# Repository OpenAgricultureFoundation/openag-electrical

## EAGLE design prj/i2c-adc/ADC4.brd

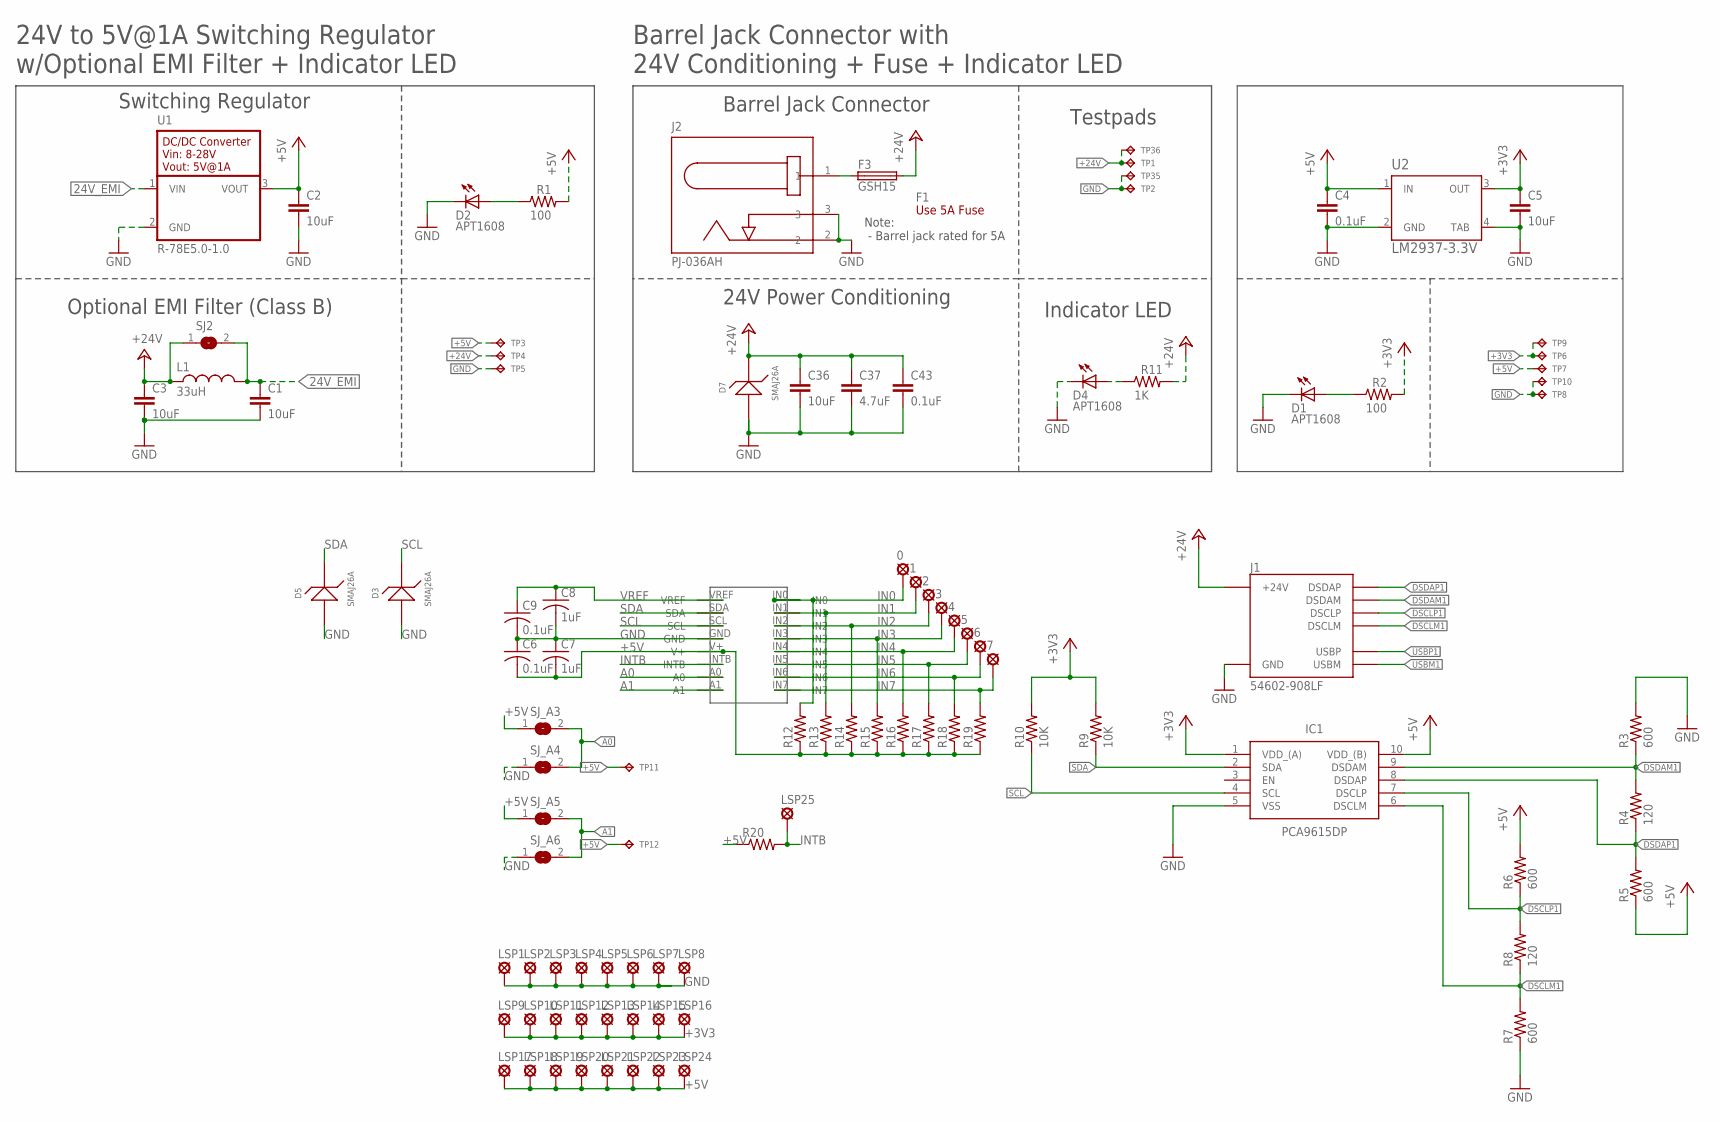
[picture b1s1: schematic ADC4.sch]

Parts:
0, 1, 2, 3, 4, 5, 6, 7: LSP13
C1, C2, C3, C5, C36: 10uF; C0805
C4, C6, C9, C43: 0.1uF; C0603
C7, C8: 1uF; C0603
C37: 4.7uF; C0805
D1, D2, D4: APT1608; CHIPLED_0603
D3, D5, D7: SMAJ26A; SMA
F1: Use 5A Fuse; FUSE-CARTRIDGE
F3: GSH15
IC1: PCA9615DP; SOP50P490X110-10N
J1: 54602-908LF; OPENAG-V1-RJ45
J2: PJ-036AH; BARREL-JACK-PJ-036AH
L1: 33uH; 29333C
LSP1, LSP2, LSP3, LSP4, LSP5, LSP6, LSP7, LSP8, LSP9, LSP10, LSP11, LSP12, LSP13, LSP14, LSP15, LSP16, LSP17, LSP18, LSP19, LSP20, LSP21, LSP22, LSP23, LSP24: LSP13
LSP25: LSP10
R1, R2: 100; RC0603N
R3, R5, R6, R7: 600; R0603
R4, R8: 120; R0603
R9, R10: 10K; R0603
R11: 1K; RC0603N
R12, R13, R14, R15, R16, R17, R18, R19, R20: R-US_R0603; R0603
SJ2: EMI-BYPASS
SJ_A3, SJ_A4, SJ_A5, SJ_A6: SOLDERJUMPERREFLOW_NOPASTE; SJ1
TP1, TP2, TP6, TP7, TP8, TP9, TP10, TP11, TP12, TP35, TP36: TPTP04R; TP04R
TP3, TP4, TP5: TPTP06R; TP06R
U1: R-78E5.0-1.0
U2: LM2937-3.3V; MP04A
U$1: ADC128D818; TSSOP16

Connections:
24V_EMI: C1.1, L1.2, SJ2.2, U1.1 (VIN)
24V_IN: F3.1, J2.1
+3V3: C5.1, IC1.1 (VDD_(A)), LSP9.MP, LSP10.MP, LSP11.MP, LSP12.MP, LSP13.MP, LSP14.MP, LSP15.MP, LSP16.MP, R2.2, R9.2, R10.2, TP6.1, TP9.1, U2.3 (OUT)
+5V: C2.1, C4.1, C6.2, C7.2, IC1.10 (VDD_(B)), LSP17.MP, LSP18.MP, LSP19.MP, LSP20.MP, LSP21.MP, LSP22.MP, LSP23.MP, LSP24.MP, R1.2, R5.1, R6.2, R12.1, R13.1, R14.1, R15.1, R16.1, R17.1, R18.1, R19.1, R20.1, SJ_A3.1, SJ_A5.1, TP3.TP, TP7.1, TP11.1, TP12.1, U1.3 (VOUT), U2.1 (IN), U$1.V+
+24V: C3.1, C36.1, C37.1, C43.1, D7.1, F3.2, J1.24V(6) (+24V), L1.1, R11.2, SJ2.1, TP1.1, TP4.TP, TP36.1
A0: SJ_A3.2, SJ_A4.2, U$1.A0
A1: SJ_A5.2, SJ_A6.2, U$1.A1
DSCLM1: IC1.6 (DSCLM), J1.DSCLM(5) (DSCLM), R7.2, R8.1
DSCLP1: IC1.7 (DSCLP), J1.DSCLP(4) (DSCLP), R6.1, R8.2
DSDAM1: IC1.9 (DSDAM), J1.DSDAM(2) (DSDAM), R3.1, R4.2
DSDAP1: IC1.8 (DSDAP), J1.DSDAP(1) (DSDAP), R4.1, R5.2
GND: C1.2, C2.2, C3.2, C4.2, C5.2, C6.1, C7.1, C8.2, C9.2, C36.2, C37.2, C43.2, D1.C, D2.C, D3.2, D4.C, D5.2, D7.2, IC1.5 (VSS), J1.GND(3) (GND), J2.2, J2.3, LSP1.MP, LSP2.MP, LSP3.MP, LSP4.MP, LSP5.MP, LSP6.MP, LSP7.MP, LSP8.MP, R3.2, R7.1, SJ_A4.1, SJ_A6.1, TP2.1, TP5.TP, TP8.1, TP10.1, TP35.1, U1.2 (GND), U2.2 (GND), U2.4 (TAB), U$1.GND
IN0: 0.MP, R12.2, U$1.IN0
IN1: 1.MP, R13.2, U$1.IN1
IN2: 2.MP, R14.2, U$1.IN2
IN3: 3.MP, R15.2, U$1.IN3
IN4: 4.MP, R16.2, U$1.IN4
IN5: 5.MP, R17.2, U$1.IN5
IN6: 6.MP, R18.2, U$1.IN6
IN7: 7.MP, R19.2, U$1.IN7
INTB: LSP25.MP, R20.2, U$1.INTB
unnamed: D1.A, R2.1
unnamed: D2.A, R1.1
unnamed: D4.A, R11.1
SCL: D3.1, IC1.4 (SCL), R10.1, U$1.SCL
SDA: D5.1, IC1.2 (SDA), R9.1, U$1.SDA
USBM1: J1.USBM(8) (USBM)
USBP1: J1.USBP(7) (USBP)
VREF: C8.1, C9.1, U$1.VREF

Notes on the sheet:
Barrel Jack Connector
Barrel Jack Connector with 24V Conditioning + Fuse + Indicator LED
24V Power Conditioning
Indicator LED
Testpads
Note: - Barrel jack rated for 5A
24V to 5V@1A Switching Regulator w/Optional EMI Filter + Indicator LED
Switching Regulator
Optional EMI Filter (Class B)

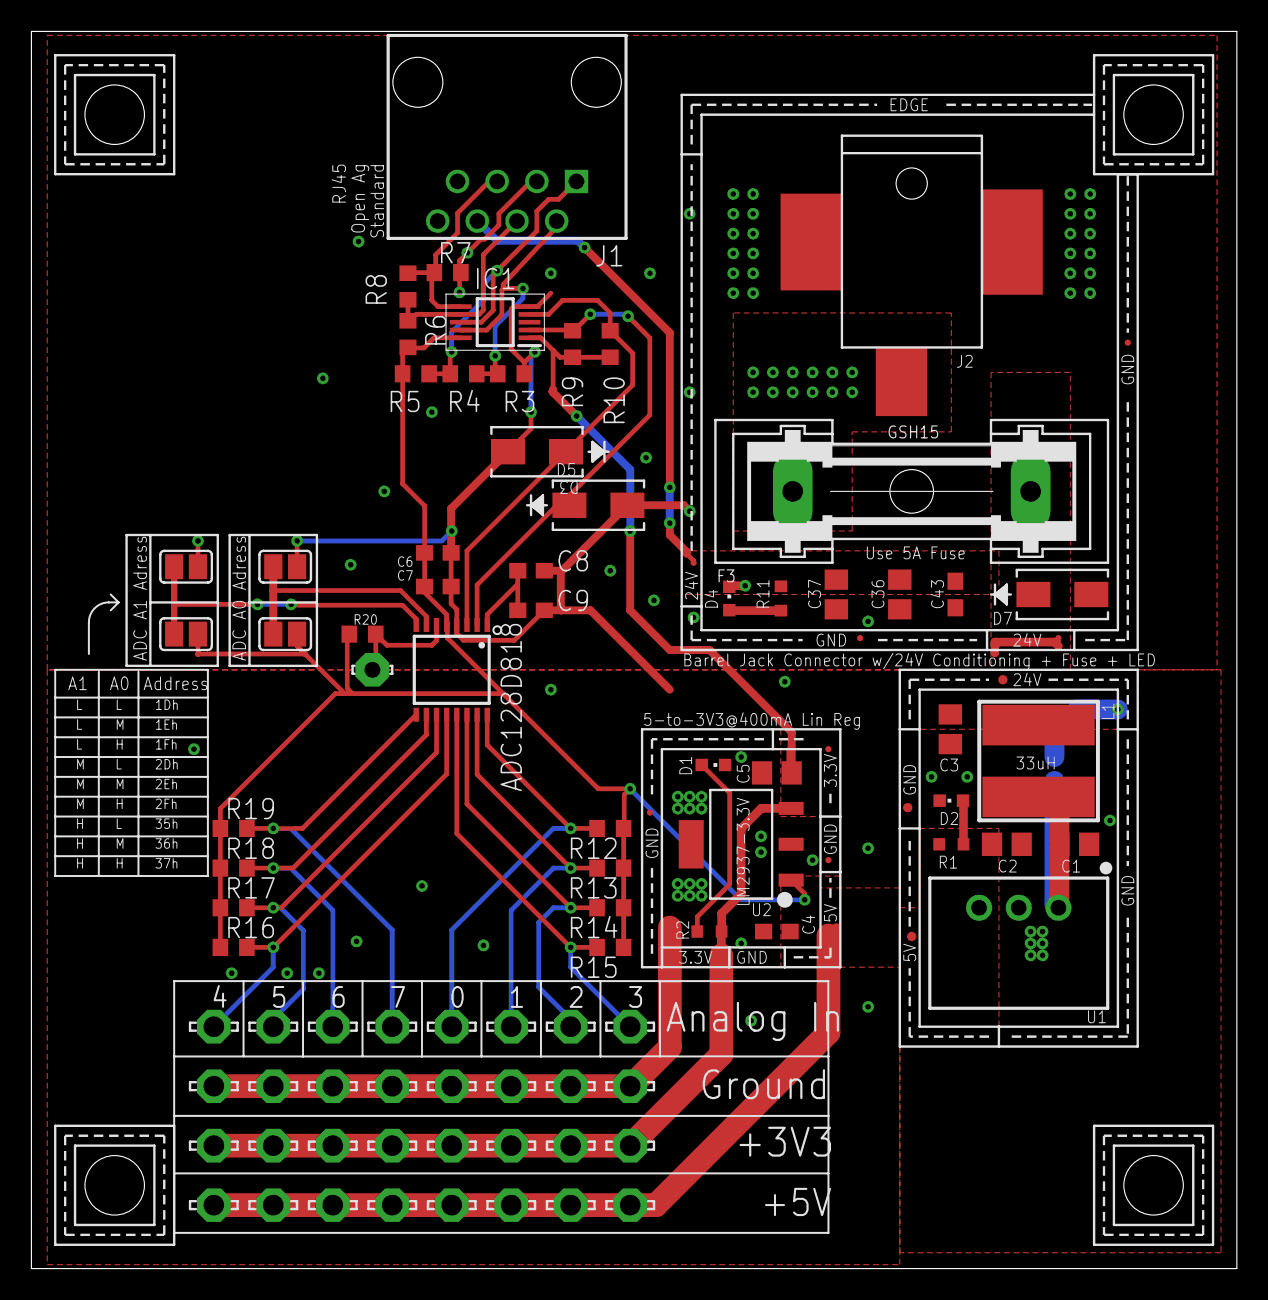
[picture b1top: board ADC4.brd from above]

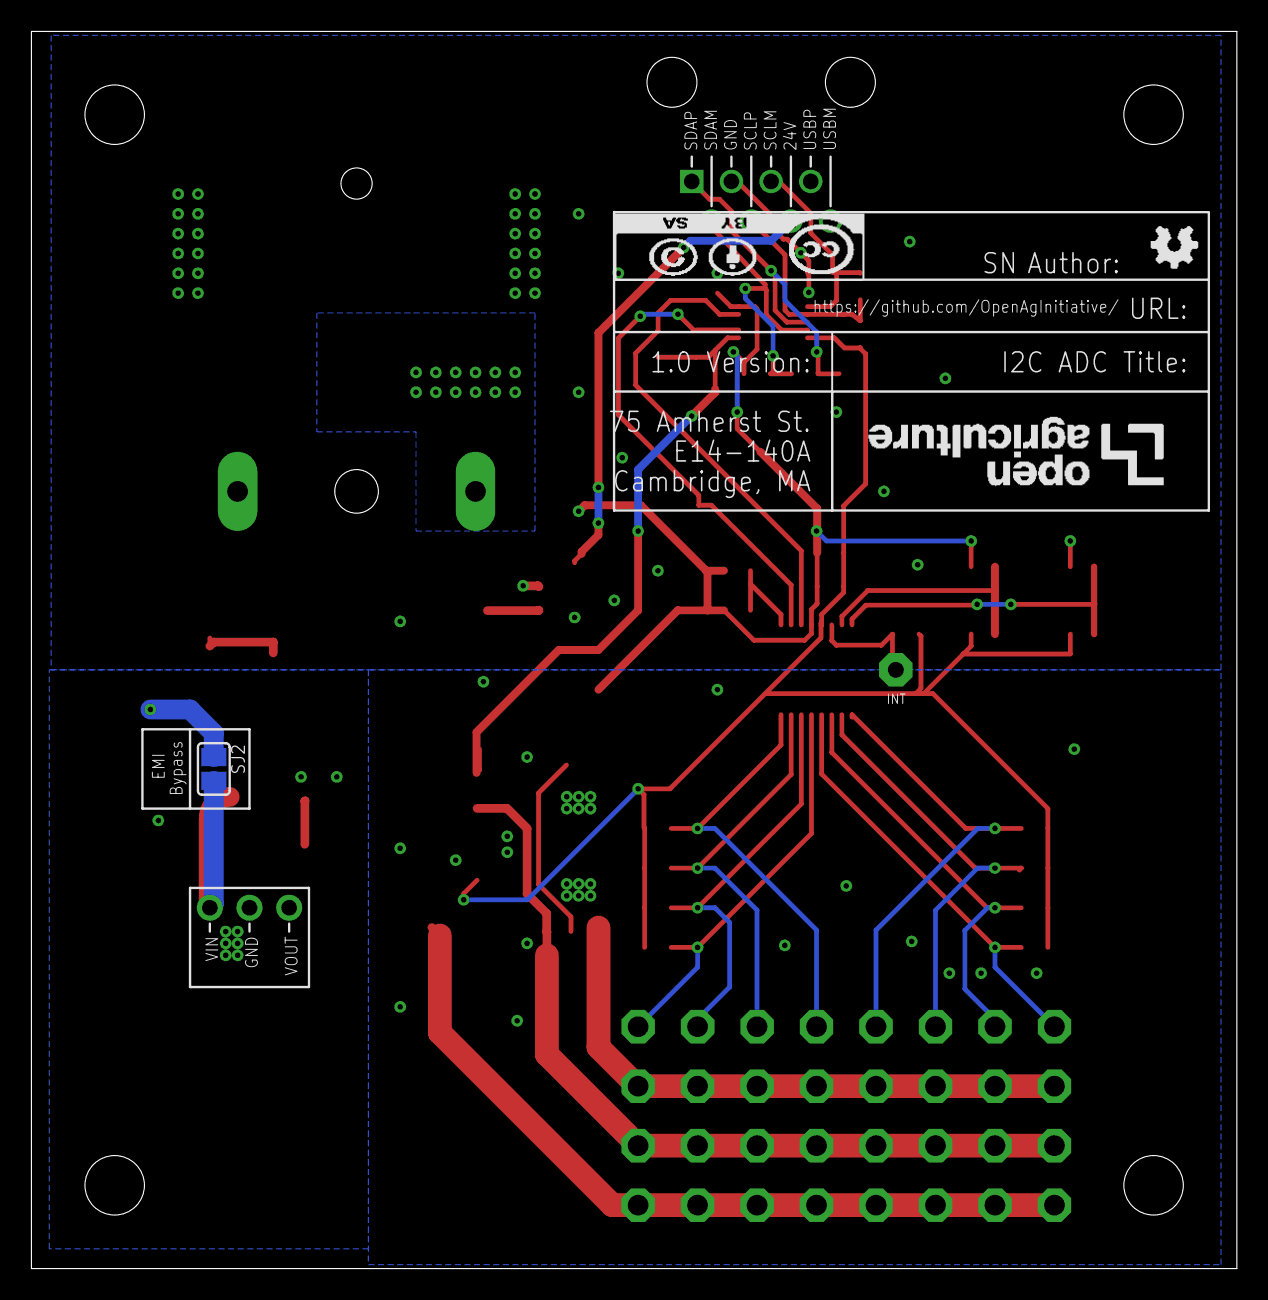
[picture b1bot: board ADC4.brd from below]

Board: 2 copper layers, 77.2 x 79.2 mm, 104 parts (2 on the bottom side), 27 nets.

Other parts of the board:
ATTRIBUTES: DOCFIELD
U$2, U$3, U$4, U$5: CORNER

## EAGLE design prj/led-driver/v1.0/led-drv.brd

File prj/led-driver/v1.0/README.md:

# LED driver board utilizing AL8861 for price and extended flexability.
### Contents
1. [Schematic](#schematic)
2. [Board Top](#board-top)
3. [Board Bottom](#board-bottom)
4. [Bill of Materials](led-drv.csv)
5. [Gerber Files](led-drv.zip)

### Schematic

### Board Top

### Board Bottom

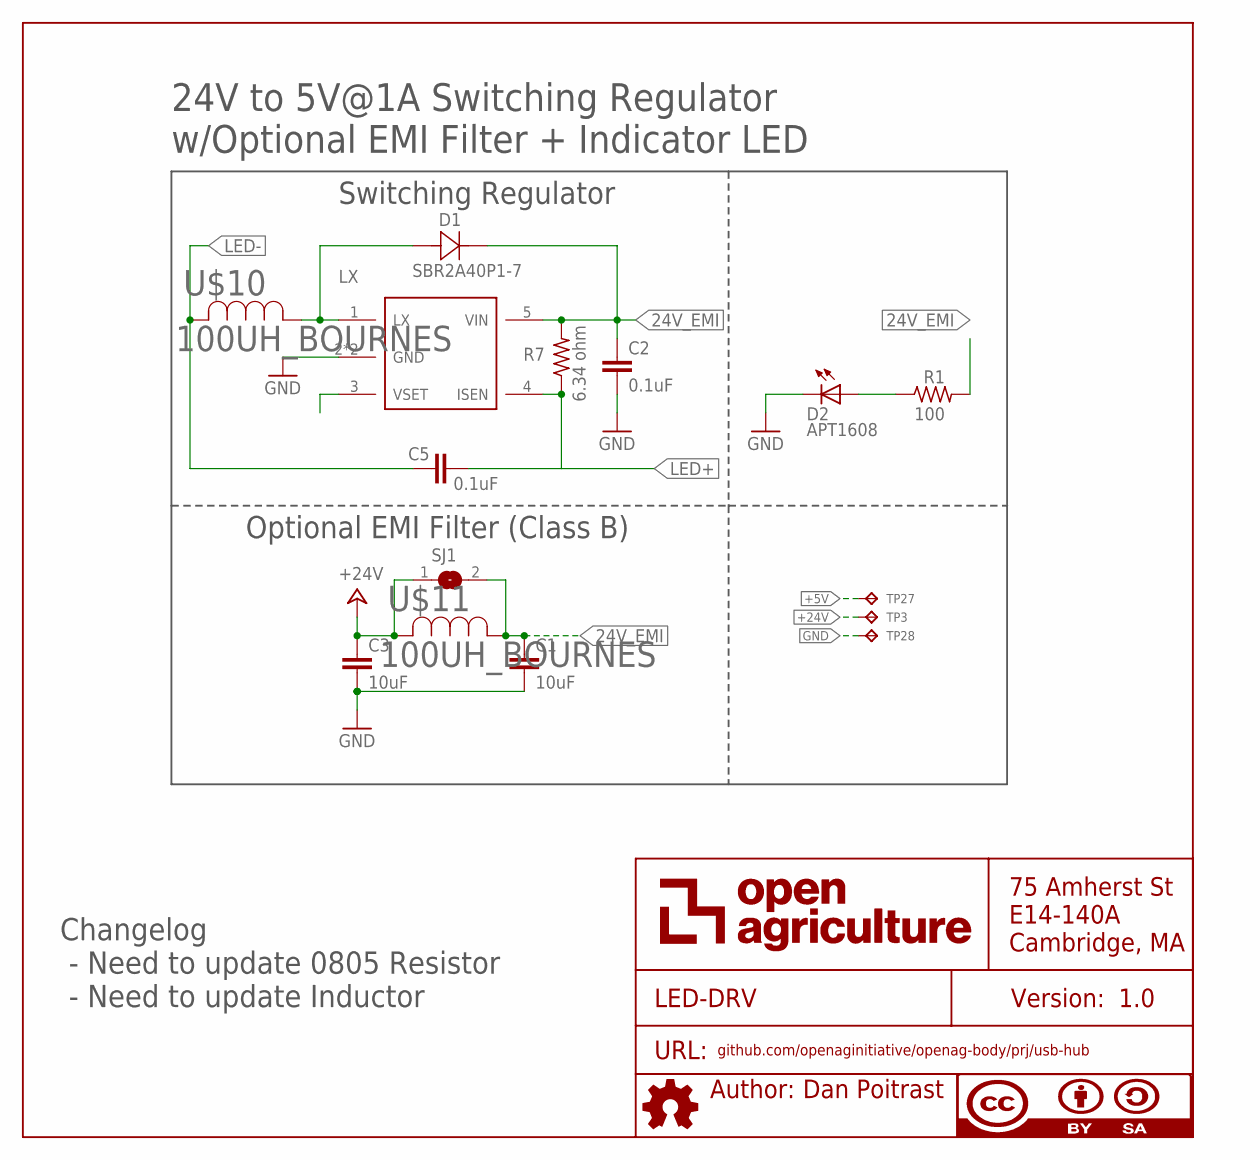
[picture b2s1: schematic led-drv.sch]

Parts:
C1, C3: 10uF; C0805
C2, C5: 0.1uF; C0603
D1: SBR2A40P1-7; POWERDI123
D2: APT1608; CHIPLED_0603
R1: 100; RC0603N
R7: 6.34 ohm; R0805
SJ1: SOLDERJUMPERREFLOW_NOPASTE; SJ1
TP3, TP27, TP28: TPTP06R; TP06R
U$6: AUTHOR
U$7: TITLE
U$9: AL8861
U$10, U$11: 100UH_BOURNES; IND_BOURNS_SDR1307

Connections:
24V_EMI: C1.1, C2.1, D1.-, R1.2, R7.2, SJ1.2, U$9.5 (VIN), U$11.1
+5V: TP27.TP
+24V: C3.1, SJ1.1, TP3.TP, U$11.2
GND: C1.2, C2.2, C3.2, D2.C, TP28.TP, U$9.2 (GND), U$9.44 (GND)
LED+: C5.2, R7.1, U$9.4 (ISEN)
LED-: C5.1, U$10.2
LX: D1.+, U$9.1 (LX), U$10.1
unnamed: D2.A, R1.1

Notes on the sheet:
24V to 5V@1A Switching Regulator w/Optional EMI Filter + Indicator LED
Switching Regulator
Optional EMI Filter (Class B)
Changelog - Need to update 0805 Resistor - Need to update Inductor

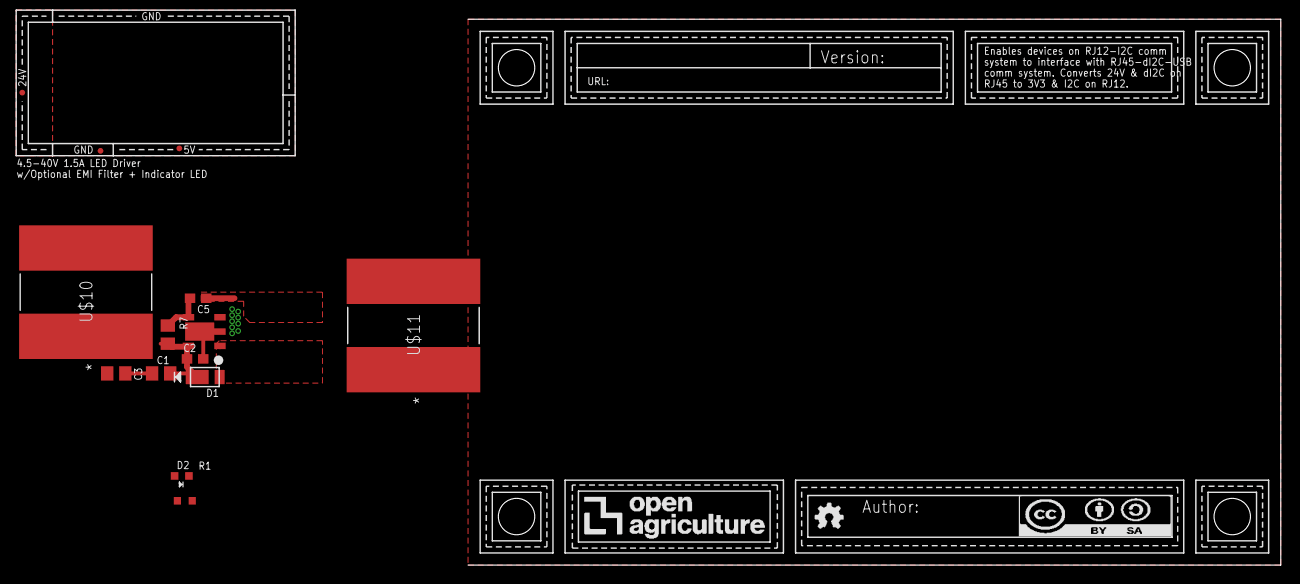
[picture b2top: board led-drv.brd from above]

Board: 2 copper layers, 22 parts (1 on the bottom side), 7 nets.

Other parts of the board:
U$1, U$2, U$3, U$4: CORNER
U$5: LOGO

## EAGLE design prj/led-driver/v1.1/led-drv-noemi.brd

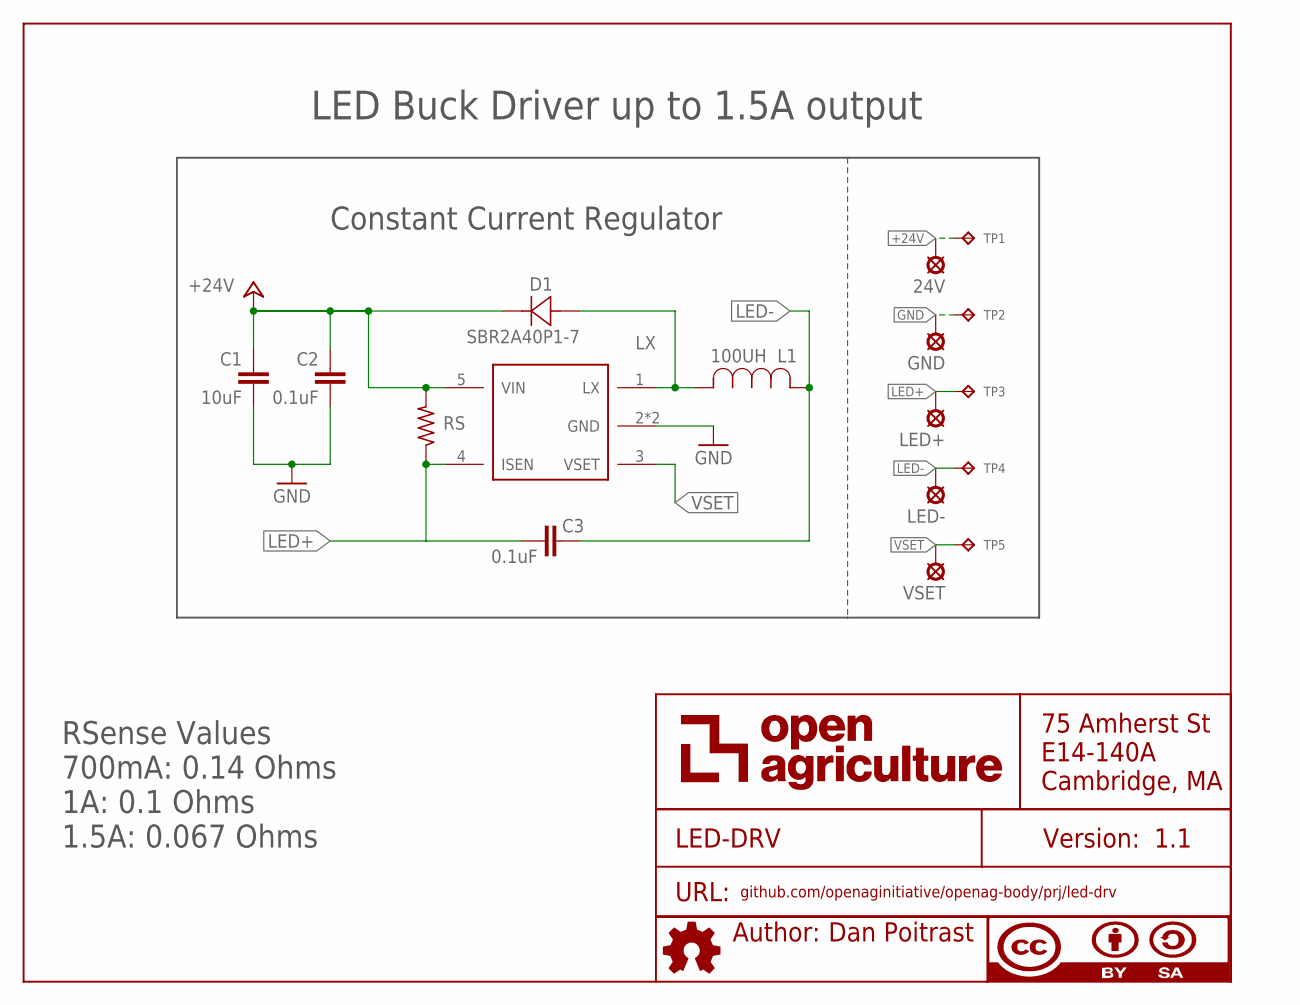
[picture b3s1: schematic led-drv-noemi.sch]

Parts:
24V: SE14
C1: 10uF; C0805
C2, C3: 0.1uF; C0603
D1: SBR2A40P1-7; POWERDI123
GND: SE14
L1: 100UH; IND_BOURNS_SDR1307
LED+: SE14
LED-: SE14
RS: .06 ohms; R0805
TP1, TP2, TP3, TP4, TP5: TPTP06R; TP06R
U$6: AUTHOR
U$7: TITLE
U$9: AL8861
VSET: SE14

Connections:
+24V: 24V.MP, C1.1, C2.1, D1.-, RS.2, TP1.TP, U$9.5 (VIN)
GND: C1.2, C2.2, GND.MP, TP2.TP, U$9.2 (GND), U$9.44 (GND)
LED+: C3.2, LED+.MP, RS.1, TP3.TP, U$9.4 (ISEN)
LED-: C3.1, L1.2, LED-.MP, TP4.TP
LX: D1.+, L1.1, U$9.1 (LX)
VSET: TP5.TP, U$9.3 (VSET), VSET.MP

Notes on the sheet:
LED Buck Driver up to 1.5A output
Constant Current Regulator
RSense Values 700mA: 0.14 Ohms 1A: 0.1 Ohms 1.5A: 0.067 Ohms

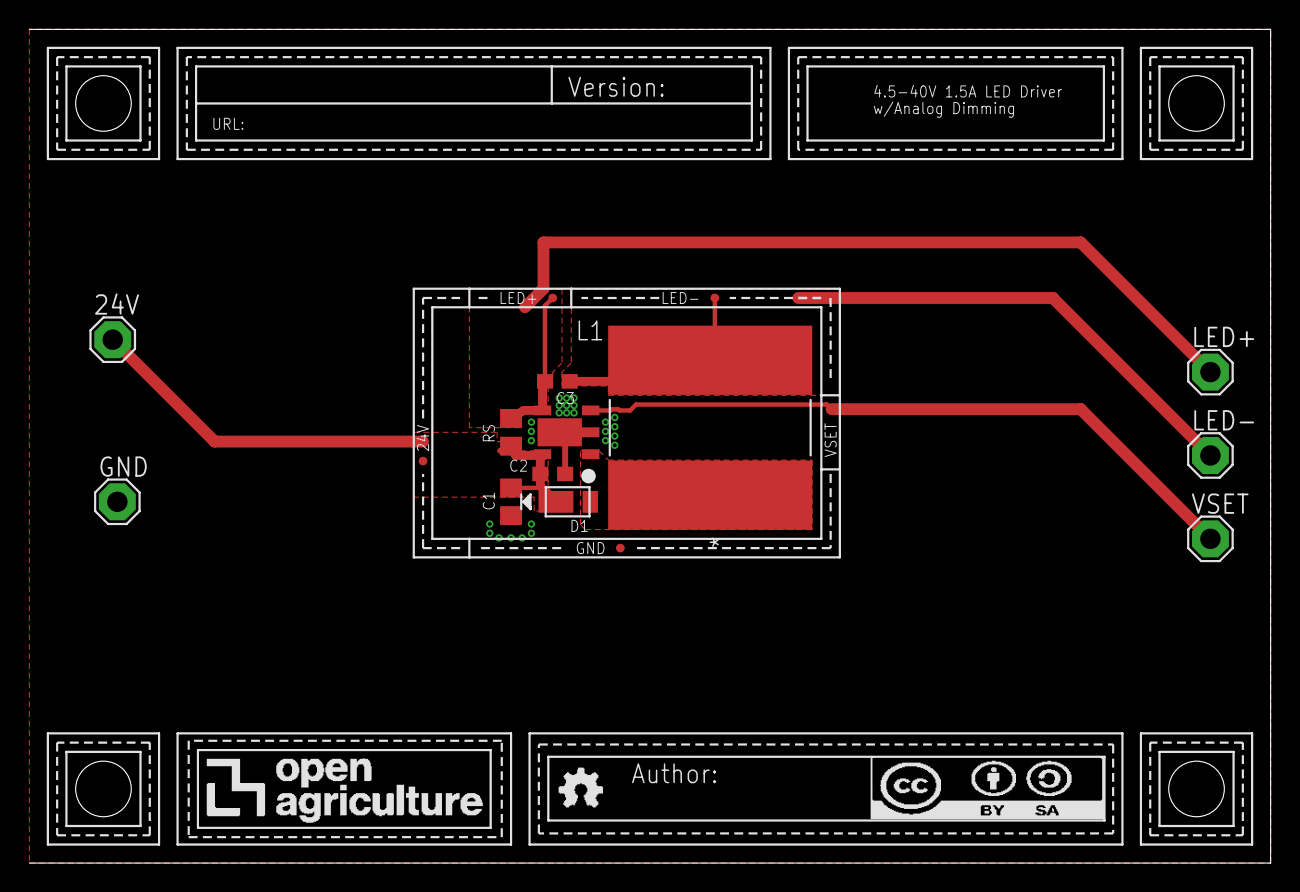
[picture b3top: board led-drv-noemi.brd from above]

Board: 2 copper layers, 85.1 x 57.1 mm, 24 parts (0 on the bottom side), 6 nets.

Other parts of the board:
U$1, U$2, U$3, U$4: CORNER
U$5: LOGO

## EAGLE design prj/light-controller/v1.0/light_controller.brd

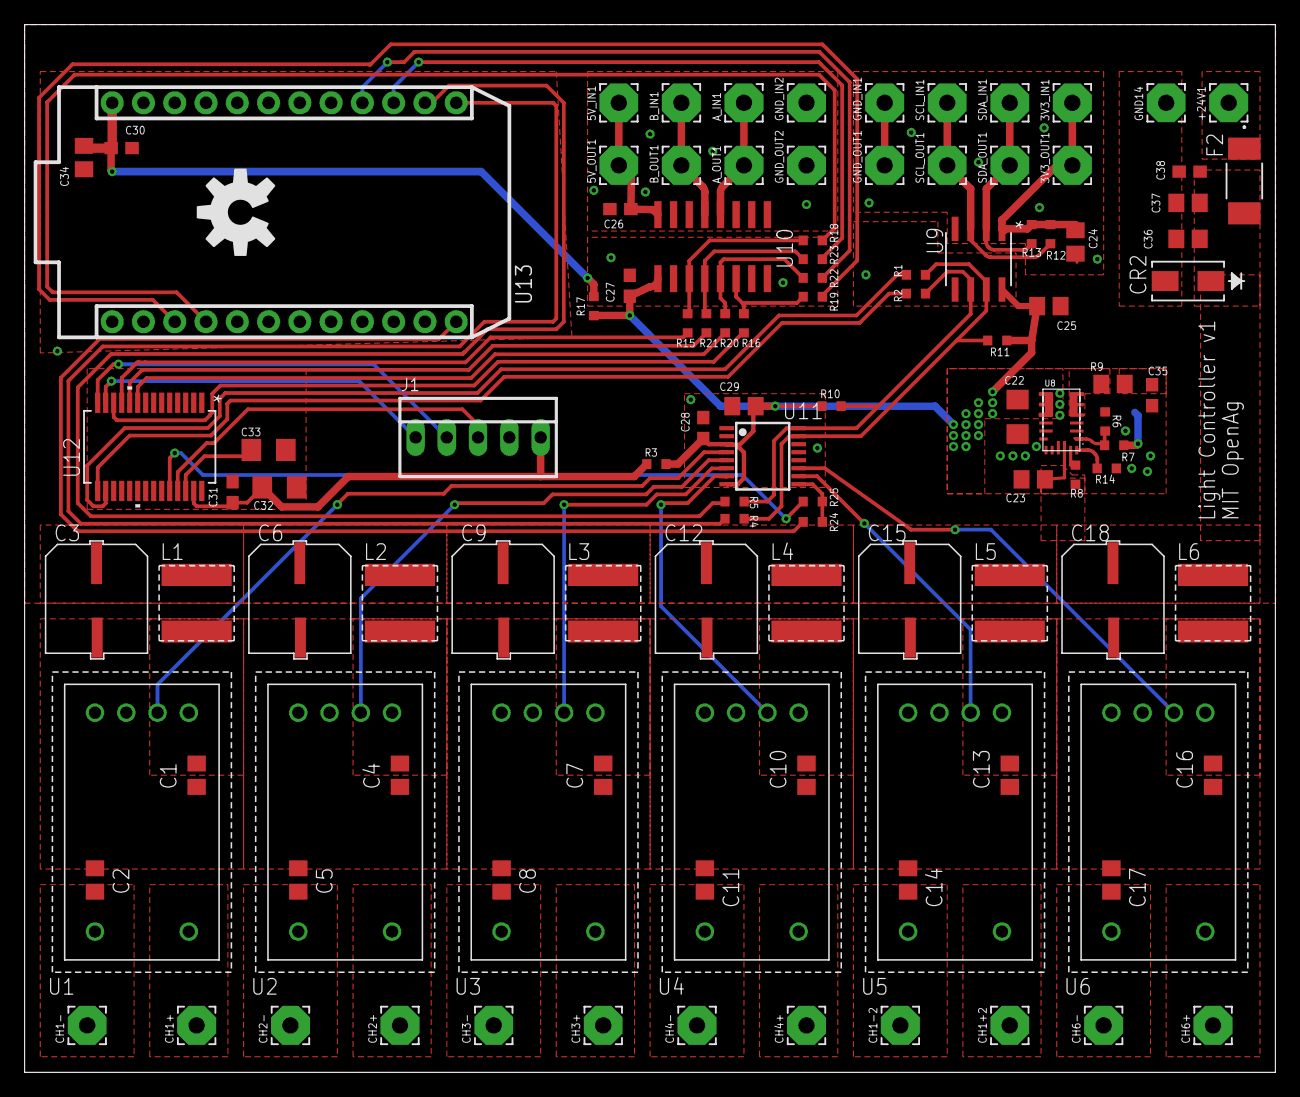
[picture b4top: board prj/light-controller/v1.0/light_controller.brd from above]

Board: 2 copper layers, 101.6 x 85.1 mm, 112 parts (0 on the bottom side), 68 nets.

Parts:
3V3_IN1, 3V3_OUT1, 5V_IN1, 5V_OUT1: 3,17/1,3
+24V1: 3,17/1,3
A_IN1: 3,17/1,3
A_OUT1: 3,17/1,3
B_IN1: 3,17/1,3
B_OUT1: 3,17/1,3
C1, C2, C4, C5, C7, C8, C10, C11, C13, C14, C16, C17, C23, C24, C25, C36: 10uF; C0805
C3, C6, C9, C12, C15, C18: 100uF; EEE-1HA101UP
C22: 22uF; C1206
C26, C27, C28, C30, C31, C38: 0.1uF; C0603
C29, C34, C37: 4.7uF; C0805
C32, C33: 1uF; C1206
C35: 330pF; C0603
CH1+, CH1+2, CH1-, CH1-2, CH2+, CH2-, CH3+, CH3-, CH4+, CH4-, CH6+, CH6-: 3,17/1,3
CR2: SMAJ26A-13-F; SMA
F2: SST 7; SS
GND14: 3,17/1,3
GND_IN1, GND_IN2: 3,17/1,3
GND_OUT1, GND_OUT2: 3,17/1,3
J1: 0022232051; 22-23-2051
L1, L2, L3, L4, L5, L6: 120uH; 74404064121
LOGO1: OSHW-LOGOL; OSHW-LOGO-L
R1, R2, R3, R4, R5, R15, R16, R17, R18, R19, R20, R21, R22, R23, R24, R25: 0 OHM; RC0603N
R6: 51K; RC0603N
R7: 160K; RC0603N
R8: 200K; RC0603N
R9: 6.34 ohm; R0805
R10, R11, R12, R13: 1K; RC0603N
R14: 16.5K; RC0603N
SCL_IN1: 3,17/1,3
SCL_OUT1: 3,17/1,3
SDA_IN1: 3,17/1,3
SDA_OUT1: 3,17/1,3
U1, U2, U3, U4, U5, U6: RCD-24-0.70; RCD-24-PINNED
U8: MPM3620GQV-P; 20-POWERLFQFN-MODULE
U9: ISO1540DR; D8
U10: ADM2481BRWZ-RL7; SOIC16N
U11: DAC5578SPW; TSSOP16
U12: CY8C4124PVI-432; SSOP-28
U13: PHOTONH; PHOTON

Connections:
24V_IN: +24V1.1, F2.1
485_5V: 5V_IN1.1, 5V_OUT1.1, C26.1, U10.16
485_A: A_IN1.1, A_OUT1.1, U10.12
485_B: B_IN1.1, B_OUT1.1, U10.13
485_GND: C26.2, GND_IN2.1, GND_OUT2.1, U10.9, U10.10, U10.15
+3V3: C22.1, C25.1, C27.1, C28.1, C29.1, R3.1, R7.2, R10.2, R11.2, R17.2, U8.8, U9.8, U10.1, U11.3, U11.8
+24V: C3.+, C6.+, C9.+, C12.+, C15.+, C18.+, C23.1, C36.1, C37.1, C38.1, CR2.1, F2.2, L1.1, L2.1, L3.1, L4.1, L5.1, L6.1, R8.2, U8.16
CH1+: CH1+.1, U1.6
CH1-: C2.1, CH1-.1, U1.5
CH2+: CH2+.1, U2.6
CH2-: C5.1, CH2-.1, U2.5
CH3+: CH3+.1, U3.6
CH3-: C8.1, CH3-.1, U3.5
CH4+: CH4+.1, U4.6
CH4-: C11.1, CH4-.1, U4.5
CH5+: CH1+2.1, U5.6
CH5-: C14.1, CH1-2.1, U5.5
CH6+: CH6+.1, U6.6
CH6-: C17.1, CH6-.1, U6.5
DAC_!CLR!: R24.2, R25.2, U11.9
DIM1: U1.2, U11.4
DIM2: U2.2, U11.5
DIM3: U3.2, U11.6
DIM4: U4.2, U11.7
DIM5: U5.2, U11.10
DIM6: U6.2, U11.11
GND: C1.2, C2.2, C3.-, C4.2, C5.2, C6.-, C7.2, C8.2, C9.-, C10.2, C11.2, C12.-, C13.2, C14.2, C15.-, C16.2, C17.2, C18.-, C22.2, C23.2, C25.2, C27.2, C28.2, C29.2, C30.2, C31.2, C32.2, C33.2, C34.2, C35.2, C36.2, C37.2, C38.2, CR2.2, GND14.1, J1.4, R6.1, R14.1, U1.4, U2.4, U3.4, U4.4, U5.4, U6.4, U8.3, U8.12, U8.13, U8.14, U9.5, U10.2, U10.7, U10.8, U11.1, U11.14, U12.28, U13.2, U13.21
I2C_3V3: 3V3_IN1.1, 3V3_OUT1.1, C24.1, R12.2, R13.2, U9.1
I2C_GND: C24.2, GND_IN1.1, GND_OUT1.1, U9.4
I2C_SCL: R12.1, SCL_IN1.1, SCL_OUT1.1, U9.3
I2C_SDA: R13.1, SDA_IN1.1, SDA_OUT1.1, U9.2
unnamed: C1.1, L1.2, U1.1
unnamed: C4.1, L2.2, U2.1
unnamed: C7.1, L3.2, U3.1
unnamed: C10.1, L4.2, U4.1
unnamed: C13.1, L5.2, U5.1
unnamed: C16.1, L6.2, U6.1
unnamed: C30.1, C34.1, R17.1, U13.24
unnamed: R8.1, U8.17
unnamed: R6.2, R7.1, U8.1
unnamed: R9.2, U8.5
unnamed: C35.1, R9.1
unnamed: C33.1, U12.26
unnamed: R14.2, U8.18
P0[7]: R25.1, U12.24
P2[6]: R20.1, U12.9
P2[7]: R21.1, U12.10
PHOTON_A0: R24.1, U13.12
PHOTON_D2: R23.1, U13.15
PHOTON_D3: R22.1, U13.16
PHOTON_RX: R18.1, U13.4
PHOTON_SCL: R5.1, U13.14
PHOTON_SDA: R4.1, U13.13
PHOTON_TX: R19.1, U13.3
SCB0_I2C_SCL: R2.1, U12.15
SCB0_I2C_SDA: R1.1, U12.16
SCB1_RX[0]: R15.1, U12.11
SCB1_TX[0]: R16.1, U12.12
SCL: R2.2, R5.2, R10.1, U9.6, U11.16
SDA: R1.2, R4.2, R11.1, U9.7, U11.15
SWD_CLK[0]: J1.2, U12.14
SWD_IO[0]: J1.1, U12.13
UART_!RE!: R21.2, R23.2, U10.4
UART_DE: R20.2, R22.2, U10.5
UART_RX: R15.2, R18.2, U10.3
UART_TX: R16.2, R19.2, U10.6
VDDD: C31.1, C32.1, J1.5, R3.2, U12.27
XRES: J1.3, U12.25

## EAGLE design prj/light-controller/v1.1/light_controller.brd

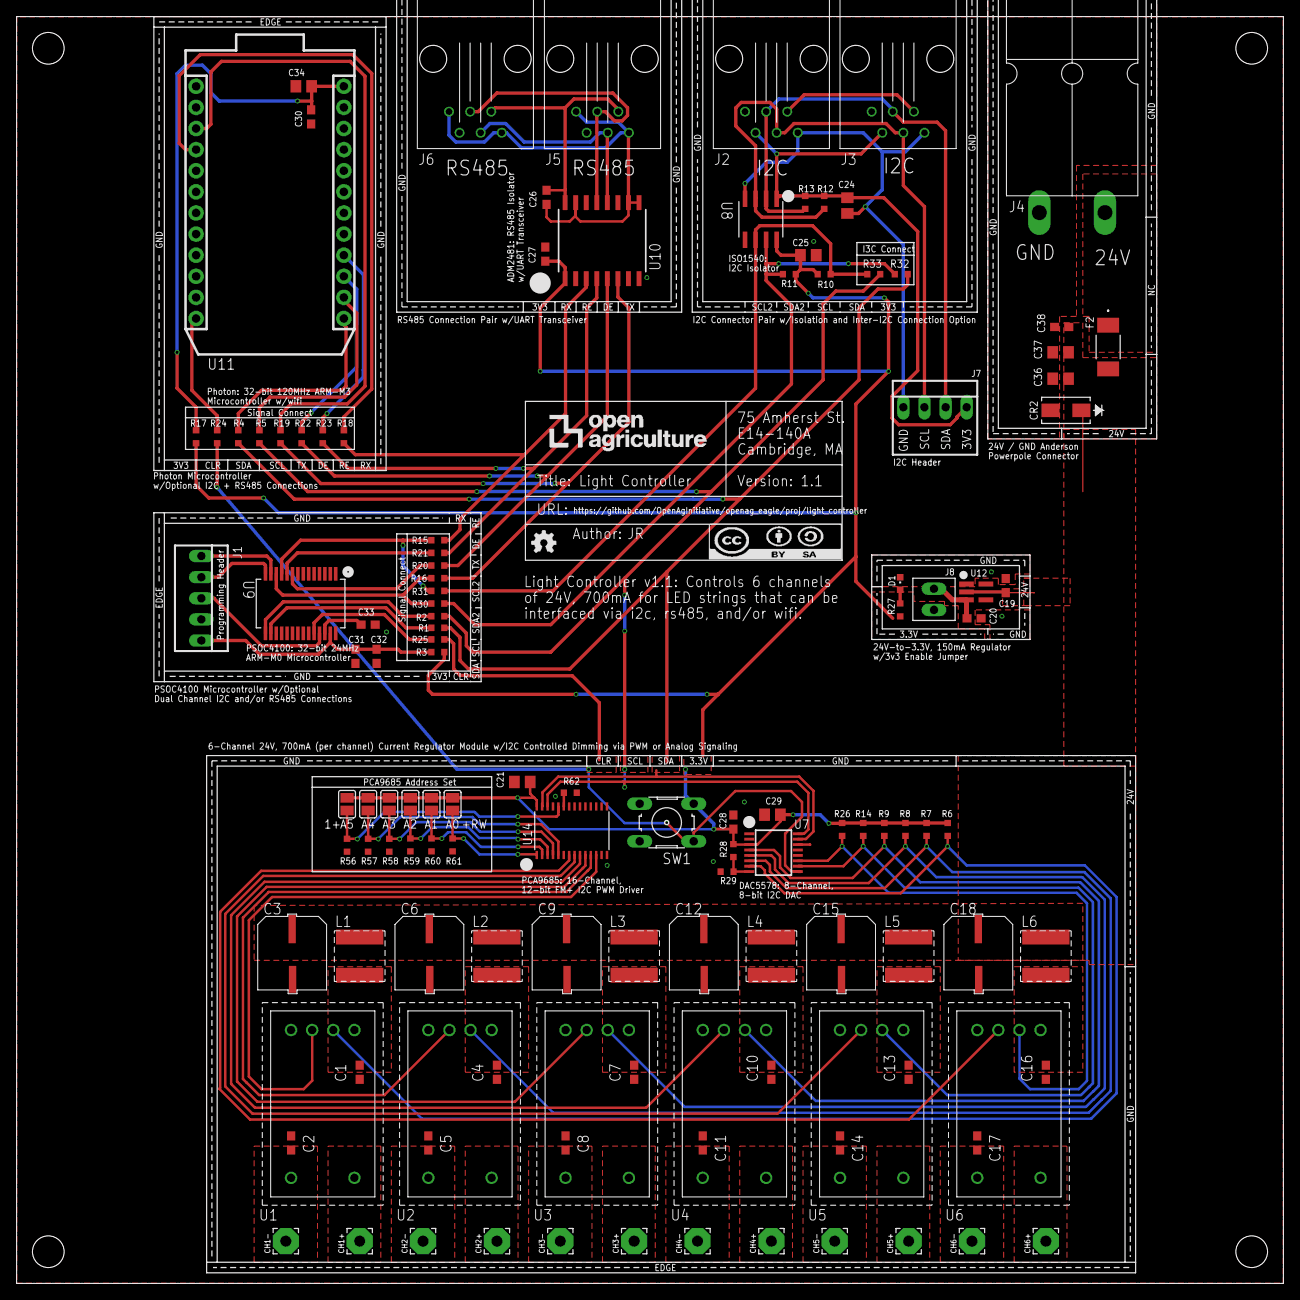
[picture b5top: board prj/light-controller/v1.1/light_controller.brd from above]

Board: 2 copper layers, 152.4 x 152.4 mm, 129 parts (0 on the bottom side), 82 nets.

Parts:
C1, C2, C4, C5, C7, C8, C10, C11, C13, C14, C16, C17: 10nF; C0603
C3, C6, C9, C12, C15, C18: 100uF; EEE-1HA101UP
C19, C26, C27, C28, C30, C31, C38: 0.1uF; C0603
C20, C32, C33: 1uF; C0603
C21, C24, C25, C36: 10uF; C0805
C29, C34, C37: 4.7uF; C0805
CH1+, CH1-, CH2+, CH2-, CH3+, CH3-, CH4+, CH4-, CH5+, CH5-, CH6+, CH6-: 3,17/1,3
CR2: SMAJ26A-13-F; SMA
D1: APT1608CGCK; CHIPLED_0603
F2: SST 7; SS
FRAME1: DOCFIELD
J1: 0022232051; 22-23-2051
J2, J3: OPENAG-I2C-RJ12
J4: 1377G2
J5, J6: OPENAG-RS485-RJ12
J7: OPENAG-I2C-HEADER
J8: JUMPER; 1X2-100-MIL-HEADER
L1, L2, L3, L4, L5, L6: 120uH; 74404064121
R1, R2, R3, R4, R5, R15, R16, R17, R18, R19, R20, R21, R22, R23, R24, R25, R30, R31, R32, R33: 0 OHM; RC0603N
R6, R7, R8, R9, R10, R11, R12, R13, R14, R26, R28: 1K; RC0603N
R27: 100 OHM; RC0603N
R29: 3.9K; RC0603N
R56, R57, R58, R59, R60, R61, R62: 10K; RC0603N
SJ_A0, SJ_A1, SJ_A2, SJ_A3, SJ_A4, SJ_A5: SOLDERJUMPER_REFLOW_NOPASTE
SW1: BF3-1020; B3F-10XX
U1, U2, U3, U4, U5, U6: RCD-24-0.70/VREF; RCD-24-PINNED
U7: DAC5578SPW; TSSOP16
U8: ISO1540DR; D8
U9: CY8C4124PVI-432; SSOP-28
U10: ADM2481BRWZ-RL7; SOIC16LWB
U11: PHOTONH; PHOTON
U12: TLV70433DBVR; DBV5-M
U14: PCA9685; TSSOP28
U$1, U$2, U$3, U$4: OPENAG-CORNER-MOUNTING-HOLE

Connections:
2.6V: R28.1, R29.2, U7.8
24V_IN: F2.1, J4.RED
485_5V: C26.1, J5.2, J6.2, U10.16
485_A: J5.3, J6.3, U10.12
485_B: J5.4, J6.4, U10.13
485_GND: C26.2, J5.1, J5.6, J6.1, J6.6, U10.9, U10.10, U10.15
+3V3: C21.1, C25.1, C27.1, C28.1, C29.1, J8.2, R3.1, R6.1, R7.1, R8.1, R9.1, R10.2, R11.2, R14.1, R17.2, R26.1, R27.2, R28.2, SJ_A0.1, SJ_A1.1, SJ_A2.1, SJ_A3.1, SJ_A4.1, SJ_A5.1, SW1.3, U7.3, U8.8, U10.1, U14.28
+24V: C3.+, C6.+, C9.+, C12.+, C15.+, C18.+, C19.1, C36.1, C37.1, C38.1, CR2.1, F2.2, L1.1, L2.1, L3.1, L4.1, L5.1, L6.1, U12.2
A0: R61.2, SJ_A0.2, U14.1
A1: R60.2, SJ_A1.2, U14.2
A2: R59.2, SJ_A2.2, U14.3
A3: R58.2, SJ_A3.2, U14.4
A4: R57.2, SJ_A4.2, U14.5
A5: R56.2, SJ_A5.2, U14.24
CH1+: CH1+.1, U1.6
CH1-: C2.1, CH1-.1, U1.5
CH2+: CH2+.1, U2.6
CH2-: C5.1, CH2-.1, U2.5
CH3+: CH3+.1, U3.6
CH3-: C8.1, CH3-.1, U3.5
CH4+: CH4+.1, U4.6
CH4-: C11.1, CH4-.1, U4.5
CH5+: CH5+.1, U5.6
CH5-: C14.1, CH5-.1, U5.5
CH6+: CH6+.1, U6.6
CH6-: C17.1, CH6-.1, U6.5
DAC_!CLR!: R24.2, R25.2, SW1.1, U7.9
DIM1: R6.2, U1.2, U7.7
DIM2: R7.2, U2.2, U7.6
DIM3: R8.2, U3.2, U7.5
DIM4: R9.2, U4.2, U7.4
DIM5: R14.2, U5.2, U7.10
DIM6: R26.2, U6.2, U7.11
GND: C1.2, C2.2, C3.-, C4.2, C5.2, C6.-, C7.2, C8.2, C9.-, C10.2, C11.2, C12.-, C13.2, C14.2, C15.-, C16.2, C17.2, C18.-, C19.2, C20.2, C21.2, C25.2, C27.2, C28.2, C29.2, C30.2, C31.2, C32.2, C33.2, C34.2, C36.2, C37.2, C38.2, CR2.2, D1.C, J1.4, J4.BLK, R29.1, R56.1, R57.1, R58.1, R59.1, R60.1, R61.1, R62.2, U1.4, U2.4, U3.4, U4.4, U5.4, U6.4, U7.1, U7.14, U8.5, U9.28, U10.2, U10.7, U10.8, U11.2, U11.21, U12.1, U14.14, U14.25
I2C_3V3: C24.1, J2.5, J3.5, J7.3V3, R12.2, R13.2, U8.1
I2C_GND: C24.2, J2.1, J3.1, J7.GND, U8.4
I2C_IO: J2.2, J3.2
unnamed: C1.1, L1.2, U1.1
unnamed: C4.1, L2.2, U2.1
unnamed: D1.A, R27.1
unnamed: C7.1, L3.2, U3.1
unnamed: C10.1, L4.2, U4.1
unnamed: C13.1, L5.2, U5.1
unnamed: C16.1, L6.2, U6.1
unnamed: C30.1, C34.1, R17.1, U11.24
unnamed: C33.1, U9.26
OE: R62.1, U14.23
P0[7]: R25.1, U9.24
P2[6]: R20.1, U9.9
P2[7]: R21.1, U9.10
PHOTON_A0: R24.1, U11.12
PHOTON_D2: R22.1, U11.15
PHOTON_D3: R23.1, U11.16
PHOTON_RX: R18.1, U11.4
PHOTON_SCL: R5.1, U11.14
PHOTON_SDA: R4.1, U11.13
PHOTON_TX: R19.1, U11.3
PWM1: U1.3, U14.12
PWM2: U2.3, U14.11
PWM3: U3.3, U14.10
PWM4: U4.3, U14.9
PWM5: U5.3, U14.8
PWM6: U6.3, U14.7
REG_3V3: C20.1, J8.1, U12.3
SCB0_I2C_SCL: R2.1, U9.15
SCB0_I2C_SDA: R1.1, U9.16
SCB1_RX[0]_SCL[0]: R15.1, R31.1, U9.11
SCB1_TX[0]_SDA[0]: R16.1, R30.1, U9.12
SCL: R2.2, R5.2, R33.2, U7.16, U14.26
SCL1: J2.3, J3.3, J7.SCL, R12.1, U8.3
SCL2: R10.1, R31.2, R33.1, U8.6
SDA: R1.2, R4.2, R32.2, U7.15, U14.27
SDA1: J2.4, J3.4, J7.SDA, R13.1, U8.2
SDA2: R11.1, R30.2, R32.1, U8.7
SWD_CLK[0]: J1.2, U9.14
SWD_IO[0]: J1.1, U9.13
UART_!RE!: R21.2, R23.2, U10.4
UART_DE: R20.2, R22.2, U10.5
UART_RX: R15.2, R18.2, U10.3
UART_TX: R16.2, R19.2, U10.6
VDDD: C31.1, C32.1, J1.5, R3.2, U9.27
XRES: J1.3, U9.25

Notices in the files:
parts and their libraries:
SparkFun-Aesthetics: Licensing: Creative Commons ShareAlike 4.0 International - https://creativecommons.org/licenses/by-sa/4.0
SparkFun-Aesthetics: Licensing: CC v3.0 Share-Alike You are welcome to use this library for commercial purposes.
